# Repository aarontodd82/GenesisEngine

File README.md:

# Genesis Engine

**Authentic Sega Genesis / Mega Drive sound on real hardware.**

The Genesis Engine is a sound board and library that brings the iconic sound of the Sega Genesis to your projects. Featuring the **YM2612 FM synthesizer** and **SN76489 PSG** chips on a board easily controlled by Teensy/Arduino/ESP32

Play VGM music files, stream audio directly from an emulator, or use it as a standalone synthesizer. 

## The Board

Schematics, KiCad, & Gerbers are in the hardware folder, but if you just want to grab one:
[https://www.tindie.com/products/40905/](https://www.tindie.com/products/40905/)

- **Stereo output** — Full left/right channel separation
- **Accurate clocks** — Crystal oscillators tuned for correct pitch
- **FM and PSG in tune** — Both chips share a proper clock relationship
- **Upgraded Op-amp** — Designed for low noise

## Features

- **Real Chips** — YM2612 FM synthesis and SN76489 PSG, not emulation
- **VGM Playback** — Play music from Genesis, Mega Drive, Game Gear, and Master System
- **Multiple Playback Modes**
  - Flash memory (PROGMEM) for standalone operation
  - SD card for large music libraries
  - Serial streaming from PC
  - Real-time streaming from emulators (BlastEm)
- **Synthesis Utilities** — Direct chip control for custom sounds, MIDI synths, and sound effects
- **Cross-Platform** — Teensy 4.x, ESP32, Arduino Mega/Uno, and more
- **VGZ Support** — Native decompression on Teensy/ESP32
- **PCM/DAC Support** — Sampled drums and vocals on YM2612 channel 6
- **Smart Memory Management** — Automatically adapts to your board's capabilities

## Supported Systems for VGM

| System | FM Chip | PSG Chip | Support |
|--------|---------|----------|---------|
| Sega Genesis / Mega Drive | YM2612 | SN76489 | Full |
| Sega Master System | — | SN76489 | PSG only |
| Sega Game Gear | — | SN76489 | PSG only |
| ColecoVision | — | SN76489 | PSG only |
| IBM PCjr | — | SN76489 | PSG only |
| Tandy 1000 PCs | — | SN76489 | PSG only |

## Quick Start

### Wiring

Connect the Genesis Engine board to your microcontroller.

| Board Pin | Function | Arduino/Teensy | ESP32 | Configurable? |
|-----------|----------|----------------|-------|---------------|
| WR_P | PSG write strobe (active low) | 2 | 16 | Yes |
| WR_Y | YM2612 write strobe (active low) | 3 | 17 | Yes |
| IC_Y | YM2612 reset (active low) | 4 | 25 | Yes |
| A0_Y | YM2612 address/data select | 5 | 26 | Yes |
| A1_Y | YM2612 port select | 6 | 27 | Yes |
| SCK | Shift register clock | SPI | SPI | See below |
| SDI | Shift register data (MOSI) | SPI | SPI | See below |
| VCC | 5V power | — | — | — |
| GND | Ground | — | — | — |

**ESP32 Note:** GPIO 0-3 (boot/serial), 6-11 (flash), and 12/15 (boot strapping) must be avoided. The defaults above are safe for ESP32-WROOM-32 dev boards.

**SPI Pins** — By default, the library uses hardware SPI for fast data transfer. These pins are fixed per board:

| Board | SCK | SDI (MOSI) |
|-------|-----|------------|
| Teensy 4.x | 13 | 11 |
| ESP32 | 18 | 23 |
| Uno | 13 | 11 |
| Mega | 52 | 51 |

If you need different pins for SCK/SDI, set `USE_HARDWARE_SPI` to 0 in `GenesisBoard.cpp` to enable software SPI on any GPIO.

### Basic Usage

```cpp
#include <GenesisEngine.h>
#include "music.h"  // Your VGM converted to a header file

// Pin connections (directly configurable)
const uint8_t WR_P = 2, WR_Y = 3, IC_Y = 4, A0_Y = 5, A1_Y = 6;

// SCK/SDI ignored when using hardware SPI (default)
GenesisBoard board(WR_P, WR_Y, IC_Y, A0_Y, A1_Y, 0, 0);
GenesisEngine player(board);

void setup() {
    board.begin();
    player.play(music_data, music_length);
    player.setLooping(true);
}

void loop() {
    player.update();  // Call frequently for proper timing
}
```

### SD Card Playback

```cpp
#include <GenesisEngine.h>
#include <SD.h>

const uint8_t WR_P = 2, WR_Y = 3, IC_Y = 4, A0_Y = 5, A1_Y = 6;
GenesisBoard board(WR_P, WR_Y, IC_Y, A0_Y, A1_Y, 0, 0);
GenesisEngine player(board);

void setup() {
    SD.begin(BUILTIN_SDCARD);  // Teensy 4.1 built-in SD
    board.begin();
    player.playFile("/music/greenhill.vgm");
}

void loop() {
    player.update();
}
```

## Playback Modes

### Flash Memory (PROGMEM)
Store music directly in your microcontroller's flash. Convert VGM files with the included tool:

```bash
python examples/BasicPlayback/vgm2header.py song.vgm
```

### SD Card
Play VGM and VGZ files directly from SD. The SDCardPlayer example includes an interactive serial menu for browsing and playback control. Works best on Teensy or ESP32. Mega has limited support (see Platform Notes). Not supported on Arduino Uno due to RAM limits.

### Serial Streaming
Stream VGM files from your PC in real-time:

```bash
python examples/SerialStreaming/stream_vgm.py song.vgm
```

### Emulator Bridge
Stream audio directly from BlastEm or other Genesis emulators to hear games on real hardware as you play.

## Platform Notes

| Feature | Teensy 4.x | ESP32 | Mega | Uno |
|---------|------------|-------|------|-----|
| PROGMEM playback | Yes | Yes | Yes | Yes |
| Serial streaming | Yes | Yes | Yes | Yes |
| SD card | Built-in | Yes | Limited* | No |
| VGZ decompression | Native | Native | Via tools | Via tools |
| PCM buffer size | 8KB+ | 4KB | 512 bytes | 256 bytes |

**Teensy 4.x is recommended**, especially for SD card playback. It offers fast GPIO, large memory, and built-in SD on the 4.1.

**Arduino Uno/Mega Limitation:** Due to AVR's 16-bit PROGMEM addressing, flash playback is limited to ~16KB (Uno) or ~60KB (Mega). Use `--strip-dac` when converting to fit more music. Uno does not support SD card (insufficient RAM). See the BasicPlayback example README for details.

*Mega SD support requires software SPI for the shift register due to pin conflicts. Results may vary—some VGM files with heavy DAC usage may have timing issues.

**ESP32 SD Note:** When using SD cards on ESP32, the shift register must use different pins (GPIO 4/13) than other examples (GPIO 18/23) because the SD card needs the hardware SPI bus. See the SDCardPlayer README for full wiring details.

## Examples

- **BasicPlayback** — VGM playback from flash memory
- **SDCardPlayer** — SD card player with serial menu
- **SerialStreaming** — Stream music from PC over USB
- **EmulatorBridge** — Real-time audio from Genesis emulators
- **SimpleSynth** — Direct chip control demo using synthesis utilities
- **MIDISynth** — Full MIDI synthesizer with voice allocation and patch management

## Tools

Each example includes relevant Python tools:

| Tool | Location | Description |
|------|----------|-------------|
| `vgm2header.py` | examples/BasicPlayback/ | Convert VGM/VGZ to C header files |
| `vgm_prep.py` | examples/SDCardPlayer/ | Prepare VGM for SD (decompress, strip DAC) |
| `stream_vgm.py` | examples/SerialStreaming/ | Stream VGM from PC to board |

## Synthesis Utilities

For direct chip control without VGM playback, the library includes synthesis utilities in `synth/`:

```cpp
#include <GenesisBoard.h>
#include <synth/FMPatch.h>
#include <synth/FMFrequency.h>
#include <synth/PSGFrequency.h>
#include <synth/DefaultPatches.h>

GenesisBoard board(2, 3, 4, 5, 6, 13, 11);
FMPatch patch;

void setup() {
    board.begin();

    // Load a built-in FM patch
    memcpy_P(&patch, &defaultFMPatches[0], sizeof(FMPatch));
    FMPatchUtils::loadToChannel(board, 0, patch);
}

void playNote(uint8_t note) {
    FMFrequency::writeToChannel(board, 0, note);
    FMFrequency::keyOn(board, 0);
}

void stopNote() {
    FMFrequency::keyOff(board, 0);
}
```

### Available Modules

| Header | Description |
|--------|-------------|
| `synth/FMFrequency.h` | MIDI note to YM2612 frequency conversion, key on/off |
| `synth/PSGFrequency.h` | MIDI note to PSG tone values, volume control |
| `synth/FMPatch.h` | FM patch structure and loading utilities |
| `synth/PSGEnvelope.h` | Software envelope generator for PSG |
| `synth/DefaultPatches.h` | 8 built-in FM patches and 4 PSG envelopes |

See the **SimpleSynth** example for a complete demo, or **MIDISynth** for a full synthesizer implementation.

## License

LGPL-2.1 — See [LICENSE](LICENSE) for details.

## Links

- [GitHub Repository](https://github.com/fm-90s/GenesisEngine)
- [FM-90s](https://fm-90s.com)

---

*Genesis Engine is not affiliated with or endorsed by Sega. Sega Genesis and Mega Drive are trademarks of Sega Corporation.*

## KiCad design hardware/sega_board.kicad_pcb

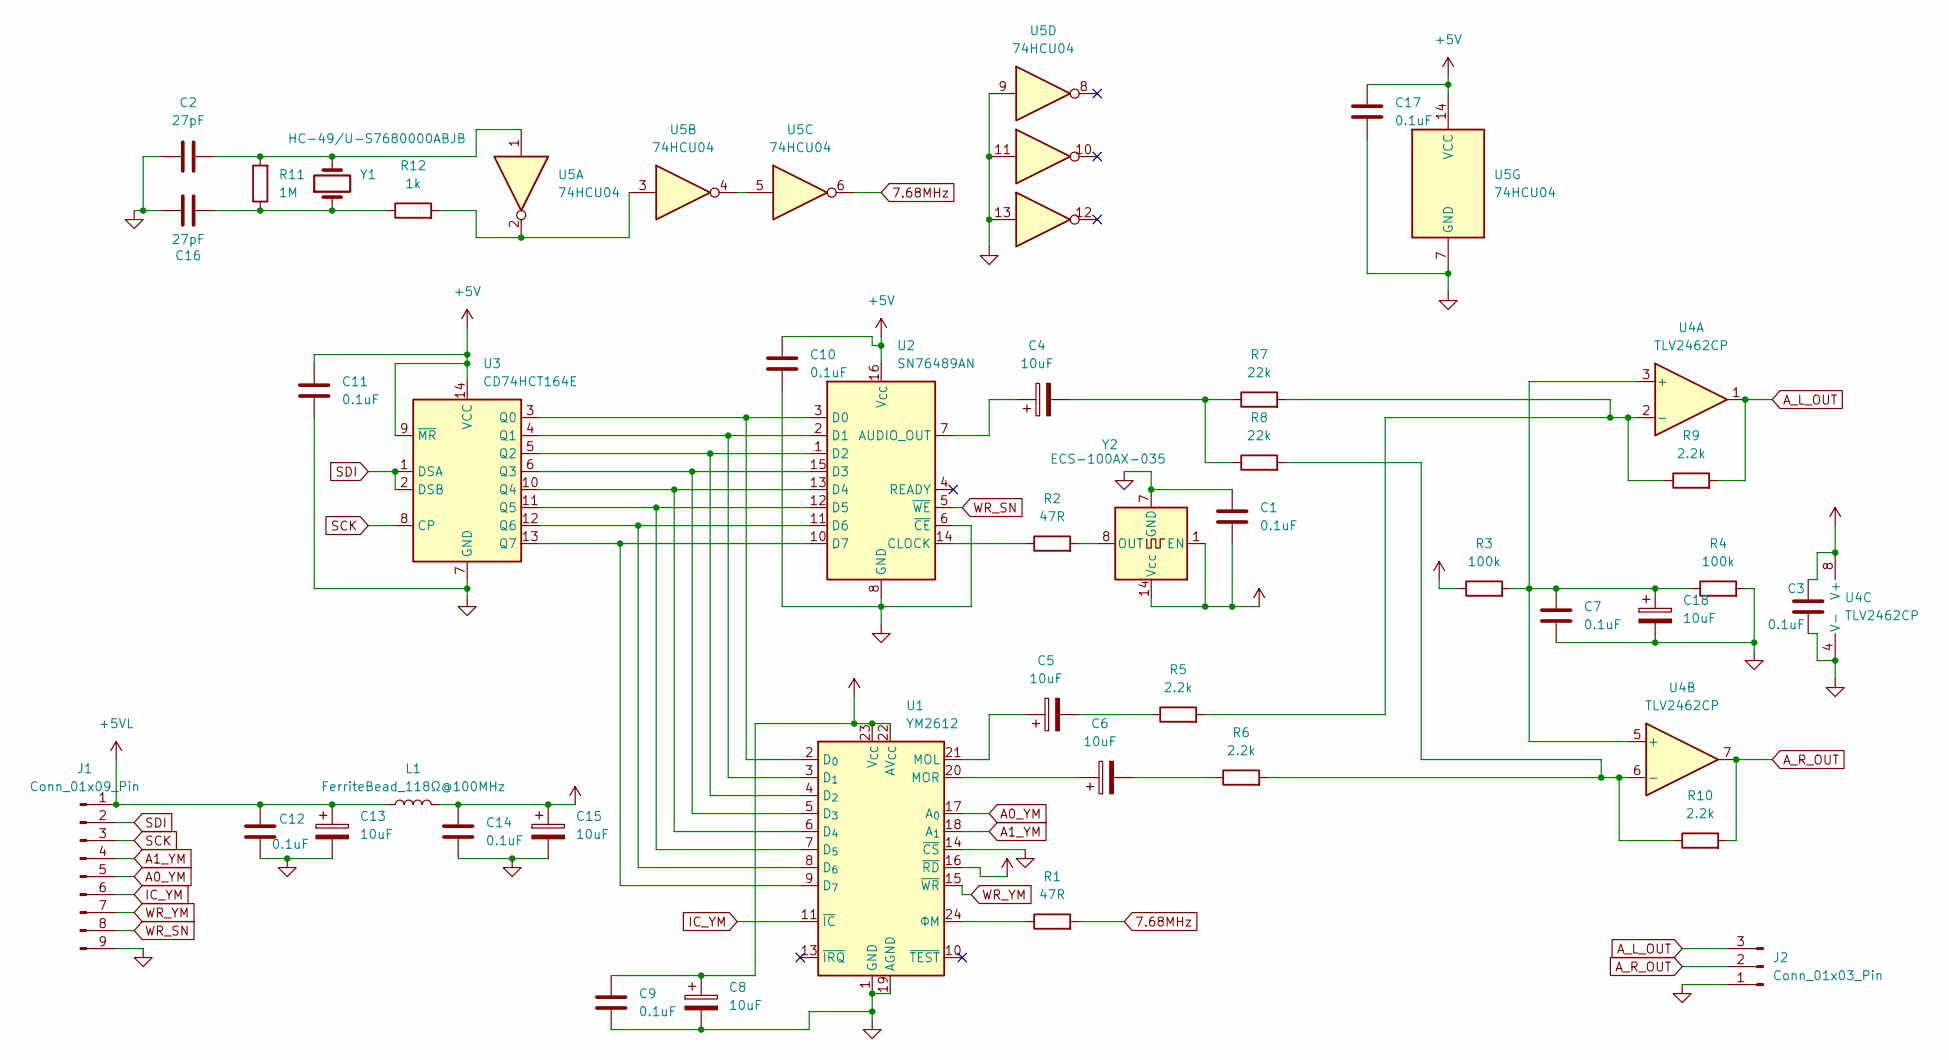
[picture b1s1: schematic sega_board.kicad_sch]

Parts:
C1, C3, C7, C9, C10, C11, C12, C14, C17: 0.1uF; C_Disc_D3.0mm_W1.6mm_P2.50mm
C2, C16: 27pF; C_Disc_D3.0mm_W1.6mm_P2.50mm
C4, C5, C6, C8, C13, C15, C18: 10uF; CP_Radial_D5.0mm_P2.00mm
J1: Conn_01x09_Pin; PinHeader_1x09_P2.54mm_Vertical
J2: Conn_01x03_Pin; PinHeader_1x03_P2.54mm_Vertical
L1: FerriteBead_118Ω@100MHz; R_Axial_DIN0207_L6.3mm_D2.5mm_P7.62mm_Horizontal; MPN 2743003112
R1, R2: 47R; R_Axial_DIN0207_L6.3mm_D2.5mm_P7.62mm_Horizontal
R3, R4: 100k; R_Axial_DIN0207_L6.3mm_D2.5mm_P7.62mm_Horizontal
R5, R6, R9, R10: 2.2k; R_Axial_DIN0207_L6.3mm_D2.5mm_P7.62mm_Horizontal
R7, R8: 22k; R_Axial_DIN0207_L6.3mm_D2.5mm_P7.62mm_Horizontal
R11: 1M; R_Axial_DIN0207_L6.3mm_D2.5mm_P7.62mm_Horizontal
R12: 1k; R_Axial_DIN0207_L6.3mm_D2.5mm_P7.62mm_Horizontal
U1: YM2612; DIP-24_W15.24mm
U2: SN76489AN; DIP-16_W7.62mm
U3: CD74HCT164E; DIP-14_W7.62mm
U4: TLV2462CP; DIP-8_W7.62mm
U5: 74HCU04; DIP-14_W7.62mm
Y1: HC-49/U-S7680000ABJB; Crystal_HC49-U_Vertical; MPN HC-49/U-S7680000ABJB
Y2: ECS-100AX-035; Oscillator_DIP-14

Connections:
7.68MHz: R1.2, U5.6
+5V: C1.2, C3.1, C8.1, C9.1, C10.1, C11.1, C14.1, C15.1, C17.1, L1.2, R3.1, U1.16 (~RD), U1.22 (AV_{CC}), U1.23 (V_{CC}), U2.16 (V_{CC}), U3.9 (~MR), U3.14 (VCC), U4.8 (V+), U5.14 (VCC), Y2.1 (EN), Y2.14 (Vcc)
+5VL: C12.1, C13.1, J1.1, L1.1
A0_YM: J1.5, U1.17 (A_{0})
A1_YM: J1.4, U1.18 (A_{1})
A_L_OUT: J2.3, R9.2, U4.1
A_R_OUT: J2.2, R10.2, U4.7
GND: C1.1, C2.1, C3.2, C7.2, C8.2, C9.2, C10.2, C11.2, C12.2, C13.2, C14.2, C15.2, C16.1, C17.2, C18.2, J1.9, J2.1, R4.2, U1.1 (GND), U1.12 (GND), U1.14 (~CS), U1.19 (AGND), U2.6 (~CE), U2.8 (GND), U3.7 (GND), U4.4 (V-), U5.7 (GND), U5.9, U5.11, U5.13, Y2.7 (GND)
IC_YM: J1.6, U1.11 (~IC)
unnamed: C2.2, R11.2, U5.1, Y1.2
unnamed: C4.2, R7.1, R8.1
unnamed: C5.2, R5.1
unnamed: C6.2, R6.1
unnamed: C16.2, R11.1, R12.1, Y1.1
unnamed: R12.2, U5.2, U5.3
unnamed: U1.2 (D_{0}), U2.3 (D0), U3.3 (Q0)
unnamed: U1.3 (D_{1}), U2.2 (D1), U3.4 (Q1)
unnamed: U1.4 (D_{2}), U2.1 (D2), U3.5 (Q2)
unnamed: U1.5 (D_{3}), U2.15 (D3), U3.6 (Q3)
unnamed: U1.6 (D_{4}), U2.13 (D4), U3.10 (Q4)
unnamed: U1.7 (D_{5}), U2.12 (D5), U3.11 (Q5)
unnamed: U1.8 (D_{6}), U2.11 (D6), U3.12 (Q6)
unnamed: U1.9 (D_{7}), U2.10 (D7), U3.13 (Q7)
unnamed: C5.1, U1.21 (MOL)
unnamed: C6.1, U1.20 (MOR)
unnamed: R1.1, U1.24 (ΦM)
unnamed: C4.1, U2.7 (AUDIO_OUT)
unnamed: R2.1, U2.14 (CLOCK)
unnamed: C7.1, C18.1, R3.2, R4.1, U4.3 (+), U4.5 (+)
unnamed: R5.2, R7.2, R9.1, U4.2 (-)
unnamed: R6.2, R8.2, R10.1, U4.6 (-)
unnamed: U5.4, U5.5
unnamed: R2.2, Y2.8 (OUT)
SCK: J1.3, U3.8 (CP)
SDI: J1.2, U3.1 (DSA), U3.2 (DSB)
WR_SN: J1.8, U2.5 (~WE)
WR_YM: J1.7, U1.15 (~WR)

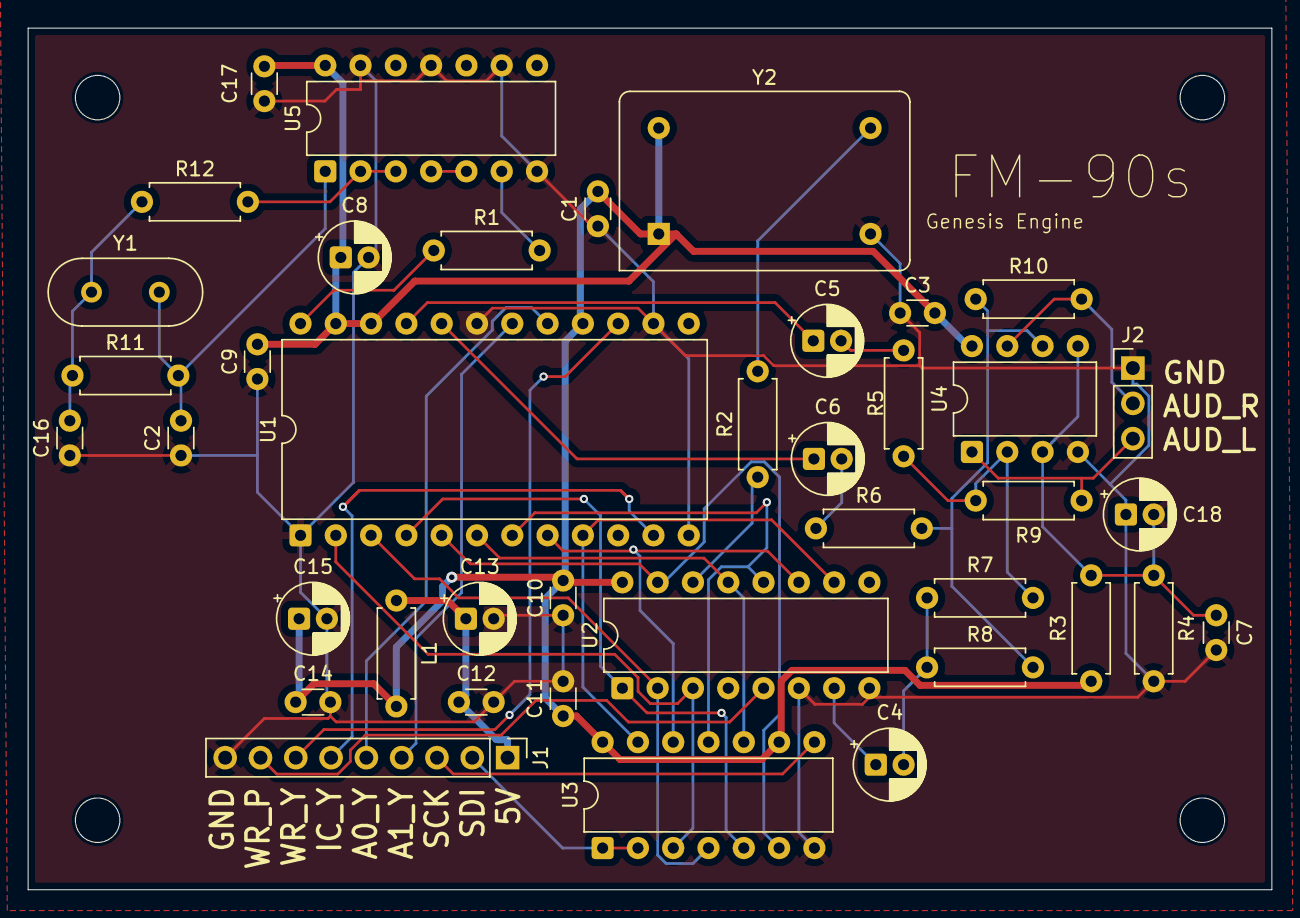
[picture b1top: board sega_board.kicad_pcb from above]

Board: 2 copper layers, 89.5 x 62.0 mm, 44 parts (0 on the bottom side), 37 nets.

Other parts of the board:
H1, H2, H3, H4: MountingHole_3.2mm_M3

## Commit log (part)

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2025-12-07 Working serial streaming with inline delays
2025-12-07 Shorter timeouts in receiveChunk for better playback timing
2025-12-08 Optimize streaming with larger buffers, non-blocking receive, and DAC options
    Arduino:
    - Larger buffers: Uno 512B, Mega 2KB (was 256/512)
    - 75% buffer fill before playback starts
    - Fully non-blocking state machine for receiving chunks
    - Pipelined ACKs during playback, immediate ACKs during buffering
    - Fixed DAC command conflict (removed unused CMD_DAC_DATA_BLOCK)
2025-12-08 Increase serial buffer and bulk read optimization
    - Increase serial RX buffer (256 for Mega, 128 for Uno)
    - Bulk read chunk data when multiple bytes available
    - Change default baud to 230400
2025-12-08 Smart timing catch-up, 500k baud, process 16 commands per serial check
    - Add smart wait timing: accumulate from scheduled time, snap to now if behind
    - Increase baud to 500000 for higher throughput
    - Process 16 commands between serial checks (was 8)
    - Eliminates jitter and tempo drift during DAC-heavy playback
2025-12-08 Add VGM looping support with native loop point detection
    - Parse VGM loop offset (0x1C) and loop samples (0x20) from header
    - Track loop point index through all preprocessing stages
    - Support --loop for infinite looping, --loop N for N plays
    - Seamless loop transitions without waiting for pending ACKs
    - Honor native VGM loop points when present, restart from beginning otherwise
2025-12-08 Board-specific flow control settings, Arduino announces board type
    - Arduino sends BOARD_TYPE during handshake
    - Python uses board-specific chunk size and chunks-in-flight
    - Uno: 64-byte chunks, 1 in-flight (fixes buffer overflow during initial fill)
    - Mega: 128-byte chunks, 3 in-flight
    - Added debug stats for chunks sent vs NAKs
2025-12-08 Clean up comments and generalize board references
    - Rewrite SerialStreaming.ino header with clear pin connections and usage
    - Change Arduino-specific references to generic device/board terminology
    - Add ESP32 to supported boards list and SPI pin table
    - Update StreamingProtocol.h comments for consistency
2025-12-09 Add SD card playback with VGZ streaming and dynamic PCM memory
    - Add SDSource for streaming VGM files directly from SD card
    - Add VGZSource for streaming gzip-compressed VGZ files with loop support
    - Add PCMDataBank for dynamic PCM/DAC memory allocation:
    - Tries PSRAM first on Teensy 4.1, falls back to RAM
    - Automatically downsamples (2x, 4x) if memory is limited
    - Gracefully disables DAC with warning if no memory available
2025-12-09 Fix VGZ looping by using relative seek positions
    VGZ looping was broken because VGMParser::seekToLoop() was seeking
    to absolute file positions while VGZSource expects relative positions
    after setDataStart() is called. This matches how MIDI-Player handles
    looping.
    Changes:
    - Add loopOffsetInData_ to VGMParser (position relative to data start)
2025-12-09 Fix README examples with proper pin definitions
2025-12-10 Fix DAC audio - pace writes to prevent sample loss
    When batched data arrives, multiple DAC writes could execute
    back-to-back with only ~5µs between them. But YM2612 DAC at
    22kHz needs ~45µs between samples or values get overwritten
    before the chip's internal sample tick captures them.
    - Add 45µs minimum spacing between DAC writes
    - Use fast writeDAC() path for register 0x2A
2025-12-10 Fix false PING detection causing audio resets
    - Change PING byte from 0x00 to 0xAA (0x00 appeared in DAC samples)
    - Only check for PING when not connected
    - END_STREAM resets hardware but stays connected
    - Disable timeout (was firing during ROM load gaps)
2025-12-11 MIDISynth: Fix poly mode velocity and add mode switching
    - Fix poly mode velocity bug: update fmChannelPatch[] when entering
    poly mode so velocity calculations use correct patch TL values
    - Fix poly mode patch loading: update all 6 channels when loading
    a patch in poly mode via SysEx
    - Add poly/multi commands to genesis_patch.py for easy mode switching
    - Change user-facing numbers to 1-based (channels 1-6, slots 1-16)
2025-12-13 BasicPlayback: Fix PROGMEM loop seeking and improve vgm2header.py
    - Fix loop point seeking for PROGMEM playback by adding setDataStart()
    to ProgmemSource, matching SDSource behavior
    - vgm2header.py: Use PROGMEM for all platforms (fixes Teensy flash placement)
    - vgm2header.py: Fix loop offset when using --strip-dac
    - vgm2header.py: Update platform size limits to be more practical
    - Add README with usage instructions
2025-12-14 SerialStreaming: Move Python tools to example directories, add README
    - Move stream_vgm.py to examples/SerialStreaming/
    - Move vgm_prep.py to examples/SDCardPlayer/
    - Add README.md documenting usage and protocol
    - Update platformio.ini to build SerialStreaming example
2025-12-14 SDCardPlayer: Add playlist support with shuffle, loop, and auto-start
    - Add playlist file format (.txt with #PLAYLIST header)
    - Support :shuffle and :loop directives
    - Per-track play count (e.g., song.vgm,3 plays 3 times)
    - Auto-start playlist: auto.txt plays on power-on
    - Add loop count tracking to VGMParser for play count detection
    - Show playlists in file list with numbers for easy selection
2025-12-14 MIDISynth: Add serial MIDI, sustain pedal, and pan/ams/pms support
    - Add Serial MIDI parser for Arduino Uno/Mega companion app support
    - Extend FMPatch with pan, ams, pms fields (45-byte extended format)
    - Implement sustain pedal (CC 64) with proper note release handling
    - Add All Sound Off (CC 120) and All Notes Off (CC 123)
    - Add SysEx commands for patch dump and device identification
    - Echo CCs to serial for companion app UI synchronization
2025-12-14 MIDISynth: Add sample TFI patches for testing
    Includes patches from Sonic 3 - Angel Island Zone and Stage Boss themes.
2025-12-14 SDCardPlayer: Add Mega support, drop Uno due to RAM limits
    - Disable hardware SPI on AVR when SD enabled (shift register conflicts)
    - Add mega_sd environment to platformio.ini for SD card testing
    - Update documentation: Uno not supported, Mega limited, Teensy recommended
    - Fix vgm_prep.py path references in error messages
2025-12-15 ESP32: Fix compilation and PSG timing issues
    - Add delayNanoseconds shim (ESP32 doesn't have this Teensy function)
    - Fix PSG write pulse timing: 4µs → 8µs (SN76489 needs full pulse)
    - Add ESP32 free memory detection using heap_caps_get_free_size()
    - Fix VGZSource to require both VGZ and SD (avoid SD.h when not needed)
    - Add ESP32-specific pin defaults avoiding boot/flash conflicts
    - Update README with ESP32 wiring table and GPIO warnings
2025-12-15 Add synthesis utilities for direct chip control
    Extract reusable FM/PSG synthesis code from MIDISynth into src/synth/:
    - FMFrequency: MIDI note to YM2612 F-number, key on/off
    - PSGFrequency: MIDI note to PSG tone, volume control
    - FMPatch/FMOperator: Patch structures and loading utilities
    - PSGEnvelope: Software envelope generator
    - DefaultPatches: 8 FM patches, 4 PSG envelopes
2025-12-16 Fix SimpleSynth serial input, add ESP32 pins to examples
    SimpleSynth: Replace Serial.parseInt() with line-based input.
    The parseInt() function has a 1-second blocking timeout that made
    commands execute immediately. Now uses buffered input with echo
    and waits for Enter key before processing.
    EmulatorBridge, SDCardPlayer: Add ESP32 pin configuration
    matching BasicPlayback and other examples.
2025-12-16 Add ESP32 SD card support with proper pin configuration
    ESP32 SD card playback requires software SPI for the shift register
    (GPIO 4/13) since the SD card uses the hardware SPI bus (GPIO 18/23).
    The shift register has no chip select, so they cannot share pins.
    - Add esp32_sd PlatformIO environment with SD library
    - Change ESP32 shift register pins to GPIO 4/13 (below GPIO 32 for
    direct register access)
2025-12-18 Revise Genesis Engine board design details
    Updated board design section with link to purchase.
2025-12-22 Fix visualization sync by decoupling sample generation from commands
    Redesigned CommandInterceptor with two separate threads:
    - Command thread: applies chip writes immediately (fast, no blocking)
    - Sample thread: generates samples at constant 60fps rate
    This fixes the 10-15 second visualization delay that occurred when
    command processing couldn't keep up with real-time playback.
    Also re-enabled Furnace-style phase-locked waveform display with:
2025-12-22 Smarter auto-scaling to prevent waveform clipping
    - Calculate safe scale that never exceeds display bounds
    - Fast response when signal gets loud (prevent clipping)
    - Slow scale-up for smooth visual appearance
    - 5% headroom to avoid edge cases
2025-12-22 Add custom branding fonts and improve visual effects
    - Use Neuropol font for FM-90s and NiseGenesis font for Genesis Engine
    - FM-90s in cyan blue (top left), Genesis Engine in Sega red (centered)
    - Add subtle neon glow effect to branding text
    - Fix channel glow to use sqrt() for perceptually linear amplitude response
    - Remove zoom pulse effect (was too distracting)
    - Add envelope follower for smoother amplitude tracking
2025-12-22 Add pygame + OpenGL visualizer with CRT shader effects
    - New app_pygame.py with OpenGL rendering and GLSL shaders
    - CRT effects: barrel distortion, scanlines, phosphor mask, bloom
    - Amplitude-based zoom/pulse effect (applied before CRT so scanlines stay fixed)
    - Gradient glow effect on active channels using additive blending
    - Scissor clipping to prevent waveforms from spilling outside boxes
    - Same waveform triggering/stabilization logic as imgui version
2025-12-23 Add visualization loop support and improve DAC/noise display
    - Fix visualization to loop with audio playback
    - Increase DAC/noise time window to 4096 samples for better display
    - Add downsampling for scrolling channels to maintain performance
    - Fix DAC channel to show glow when active
    - Remove thick DAC line width
2025-12-23 Fix sync catch-up and add adaptive display for low frequencies
    - Fix catch-up sync: process all commands through interceptor, only skip sleep
    (skipping commands entirely broke emulator state and caused blank waveforms)
    - Add adaptive display samples based on channel pitch
    - Normal frequencies: keep default 256 samples to show frequency changes
    - Low frequencies: expand window to show ~1.5 cycles (up to 1024 samples)
2025-12-23 Remove unused ym2612 emulator and test artifacts
2025-12-23 Fix DAC output and adjust PSG mix level
2025-12-24 Sync visualization with audio by compensating for buffer latency
    - Query actual audio output latency from sounddevice stream
    - Delay visualization updates to match audio pipeline latency
    - Total delay = ring buffer fill time + system reported latency
    - Ensures waveforms, key indicators, and pitch display are in sync with audio
2025-12-24 Add fullscreen CLI option and fix audio clipping
    - Add --fullscreen/-f flag to start in fullscreen mode
    - Use borderless windowed fullscreen for OBS capture compatibility
    - Fix audio clipping by scaling FM output (0.45) and PSG (0.15)
2025-12-24 Improve portrait mode layout and fix channel box alignment
    - Reduce waveform sample count in portrait mode (128 vs 256) for less condensed display
    - Increase status bar height in portrait mode (80px vs 60px)
    - Hide status/FPS text in portrait mode to reduce clutter
    - Use larger font for metadata in portrait mode
    - Fix channel box right edge alignment to match status bar width
